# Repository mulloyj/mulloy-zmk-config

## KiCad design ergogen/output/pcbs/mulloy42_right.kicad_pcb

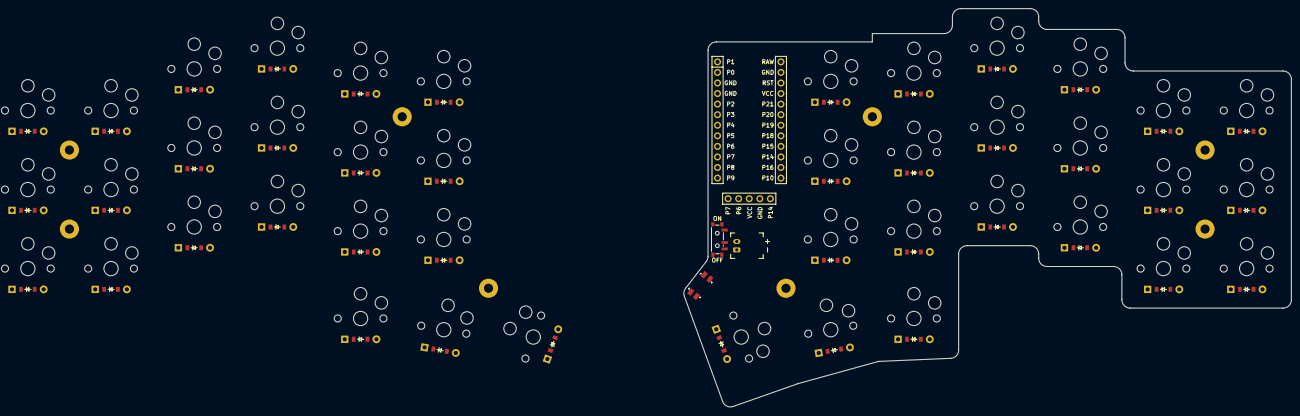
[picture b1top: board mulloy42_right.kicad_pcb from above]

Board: 2 copper layers, 146.1 x 95.8 mm, 97 parts (0 on the bottom side), 60 nets, no tracks yet.

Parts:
D1, D2, D3, D4, D5, D6, D7, D8, D9, D10, D11, D12, D13, D14, D15, D16, D17, D18, D19, D20, D21, D22, D23, D24, D25, D26, D27, D28, D29, D30, D31, D32, D33, D34, D35, D36, D37, D38, D39, D40, D41, D42: ComboDiode
DISP1: display_nice_view
JST1: battery_connector_jst_ph_2
MCU1: mcu_nice_nano
MH1, MH2, MH3, MH4, MH5, MH6, MH7, MH8: mounting_hole_npth
PWR1: power_switch_smd_side
RST1: reset_switch_smd_side
S1, S2, S3, S4, S5, S6, S7, S8, S9, S10, S11, S12, S13, S14, S15, S16, S17, S18, S19, S20, S21, S22, S23, S24, S25, S26, S27, S28, S29, S30, S31, S32, S33, S34, S35, S36, S37, S38, S39, S40, S41, S42: PG1350

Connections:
BAT_P: JST1.2, PWR1.1
GND: DISP1.4, JST1.1, MCU1.2, MCU1.21, MCU1.22, RST1.1, RST1.3
P2: MCU1.20, S16.1, S17.1, S18.1, S21.1, S37.1, S38.1, S39.1, S42.1
P3: D3.1, D6.1, D9.1, D12.1, D15.1, D18.1, D24.1, D27.1, D30.1, D33.1, D36.1, D39.1, MCU1.19
P4: D2.1, D5.1, D8.1, D11.1, D14.1, D17.1, D23.1, D26.1, D29.1, D32.1, D35.1, D38.1, MCU1.18
P5: D1.1, D4.1, D7.1, D10.1, D13.1, D16.1, D22.1, D25.1, D28.1, D31.1, D34.1, D37.1, MCU1.17
P6: DISP1.2, MCU1.16
P7: DISP1.1, MCU1.15
P8: MCU1.14, S4.1, S5.1, S6.1, S25.1, S26.1, S27.1
P9: MCU1.13, S1.1, S2.1, S3.1, S22.1, S23.1, S24.1
P10: D19.1, D20.1, D21.1, D40.1, D41.1, D42.1, MCU1.12
P14: DISP1.5, MCU1.10
P15: MCU1.9, S13.1, S14.1, S15.1, S20.1, S34.1, S35.1, S36.1, S41.1
P16: MCU1.11, S7.1, S8.1, S9.1, S28.1, S29.1, S30.1
P18: MCU1.8, S10.1, S11.1, S12.1, S19.1, S31.1, S32.1, S33.1, S40.1
RAW: MCU1.1, PWR1.2
RST: MCU1.3, RST1.2, RST1.4
VCC: DISP1.3, MCU1.4
index_bottom: D13.2, S13.2
index_home: D14.2, S14.2
index_thumb: D20.2, S20.2
index_top: D15.2, S15.2
inner_bottom: D16.2, S16.2
inner_home: D17.2, S17.2
inner_thumb: D21.2, S21.2
inner_top: D18.2, S18.2
middle_bottom: D10.2, S10.2
middle_home: D11.2, S11.2
middle_thumb: D19.2, S19.2
middle_top: D12.2, S12.2
mirror_index_bottom: D34.2, S34.2
mirror_index_home: D35.2, S35.2
mirror_index_thumb: D41.2, S41.2
mirror_index_top: D36.2, S36.2
mirror_inner_bottom: D37.2, S37.2
mirror_inner_home: D38.2, S38.2
mirror_inner_thumb: D42.2, S42.2
mirror_inner_top: D39.2, S39.2
mirror_middle_bottom: D31.2, S31.2
mirror_middle_home: D32.2, S32.2
mirror_middle_thumb: D40.2, S40.2
mirror_middle_top: D33.2, S33.2
mirror_outer_bottom: D22.2, S22.2
mirror_outer_home: D23.2, S23.2
mirror_outer_top: D24.2, S24.2
mirror_pinky_bottom: D25.2, S25.2
mirror_pinky_home: D26.2, S26.2
mirror_pinky_top: D27.2, S27.2
mirror_ring_bottom: D28.2, S28.2
mirror_ring_home: D29.2, S29.2
mirror_ring_top: D30.2, S30.2
outer_bottom: D1.2, S1.2
outer_home: D2.2, S2.2
outer_top: D3.2, S3.2
pinky_bottom: D4.2, S4.2
pinky_home: D5.2, S5.2
pinky_top: D6.2, S6.2
ring_bottom: D7.2, S7.2
ring_home: D8.2, S8.2
ring_top: D9.2, S9.2

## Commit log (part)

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2026-03-24 corne init
2026-03-24 First updates to the keymap
2026-03-28 ergogen init
2026-03-29 Adding keyboard outline to ergogen
2026-03-29 Updating to graphite layout
2026-03-29 changing the named
2026-04-01 pcb designs complete, routing required
2026-04-03 updated left/right pcb
2026-04-05 fixing zmk defs
2026-04-06 trying to fix build error
2026-04-06 new config file for mulloy42
2026-04-06 resetting the board to basic corne
2026-04-06 trying to make my own config
2026-04-06 fixing shields typo
2026-04-06 fixing module structure and missing semicolon
2026-04-06 fixing semicolon syntax and duplicate pins
2026-04-06 fixing root node issue in devicetree
2026-04-06 moving chosen node and updating it
2026-04-06 trying another fix
2026-04-06 undoing the fix?
2026-04-06 creating a zmk studio compatible layout
2026-04-06 wrong import
2026-04-06 actually fixing import
2026-04-06 fixing typos
2026-04-06 trying to get keymap-editor working
2026-04-06 removing encoders
2026-04-06 Updating keymap
2026-05-02 updated keymap
2026-05-02 final pcb designs and gerber files
2026-05-02 fixing some issues in the keymap
2026-05-02 Some more small changes
2026-05-03 some new ideas
2026-05-06 adding urob timeless homerow mods and magic shift
2026-05-06 fixing urob timeless homerow mods and magic shift
2026-05-07 adding nice!view
2026-05-08 adding nice!view pins and setting up the nice!view config
2026-05-08 fixing a typo
2026-05-08 fixing another typo
2026-05-08 removing nice!view adapter
2026-05-08 removing nice!view adapter for real
2026-05-08 fixing typo
2026-05-08 turning off zmk default screen stuff
2026-05-08 fixing nice!view
2026-05-08 fixing cols (left)
2026-05-08 fixing cols (right)
2026-05-08 syntax error
2026-05-08 syntax error and fixing pins for nice!view
2026-05-08 fixing thumb keys
2026-05-08 another attempt at fixing the nice!view
2026-05-08 still figuring out what is going on
2026-05-09 trying to fix connectivity issue
2026-05-09 fixing left thumb
2026-05-09 some setting changes
2026-05-09 actually saving my changes
2026-05-09 adding hold access to fn layer
2026-05-09 adding save as a key
2026-05-09 updating thumb keys
2026-05-11 adding 5th bluetooth profile and editing some keys
2026-05-11 adding percent to num
2026-05-11 trying some combos
2026-05-11 some more combos and some other changes
2026-05-12 adding some new combos
2026-05-12 adding some new combos, fixing missing semicolon
2026-05-13 trying something new for battery life and adding combos for command and period on the numpad
2026-05-21 adding email combo and updating meh to be osm
2026-05-27 adding some combos around brackets
2026-05-27 fixing keycodes for parentheses
2026-05-27 fixing macro character for parenthese
2026-05-27 fixing a typo and trying a fix for caps word behaviour
2026-05-28 tyring to fix repeat in parentheses macro
2026-05-28 actual fix for repeat keys
2026-06-02 adding valorant layer
2026-06-02 updating dxf to make modeling case easier
2026-06-03 adding dxf to make 3d modelling easier
